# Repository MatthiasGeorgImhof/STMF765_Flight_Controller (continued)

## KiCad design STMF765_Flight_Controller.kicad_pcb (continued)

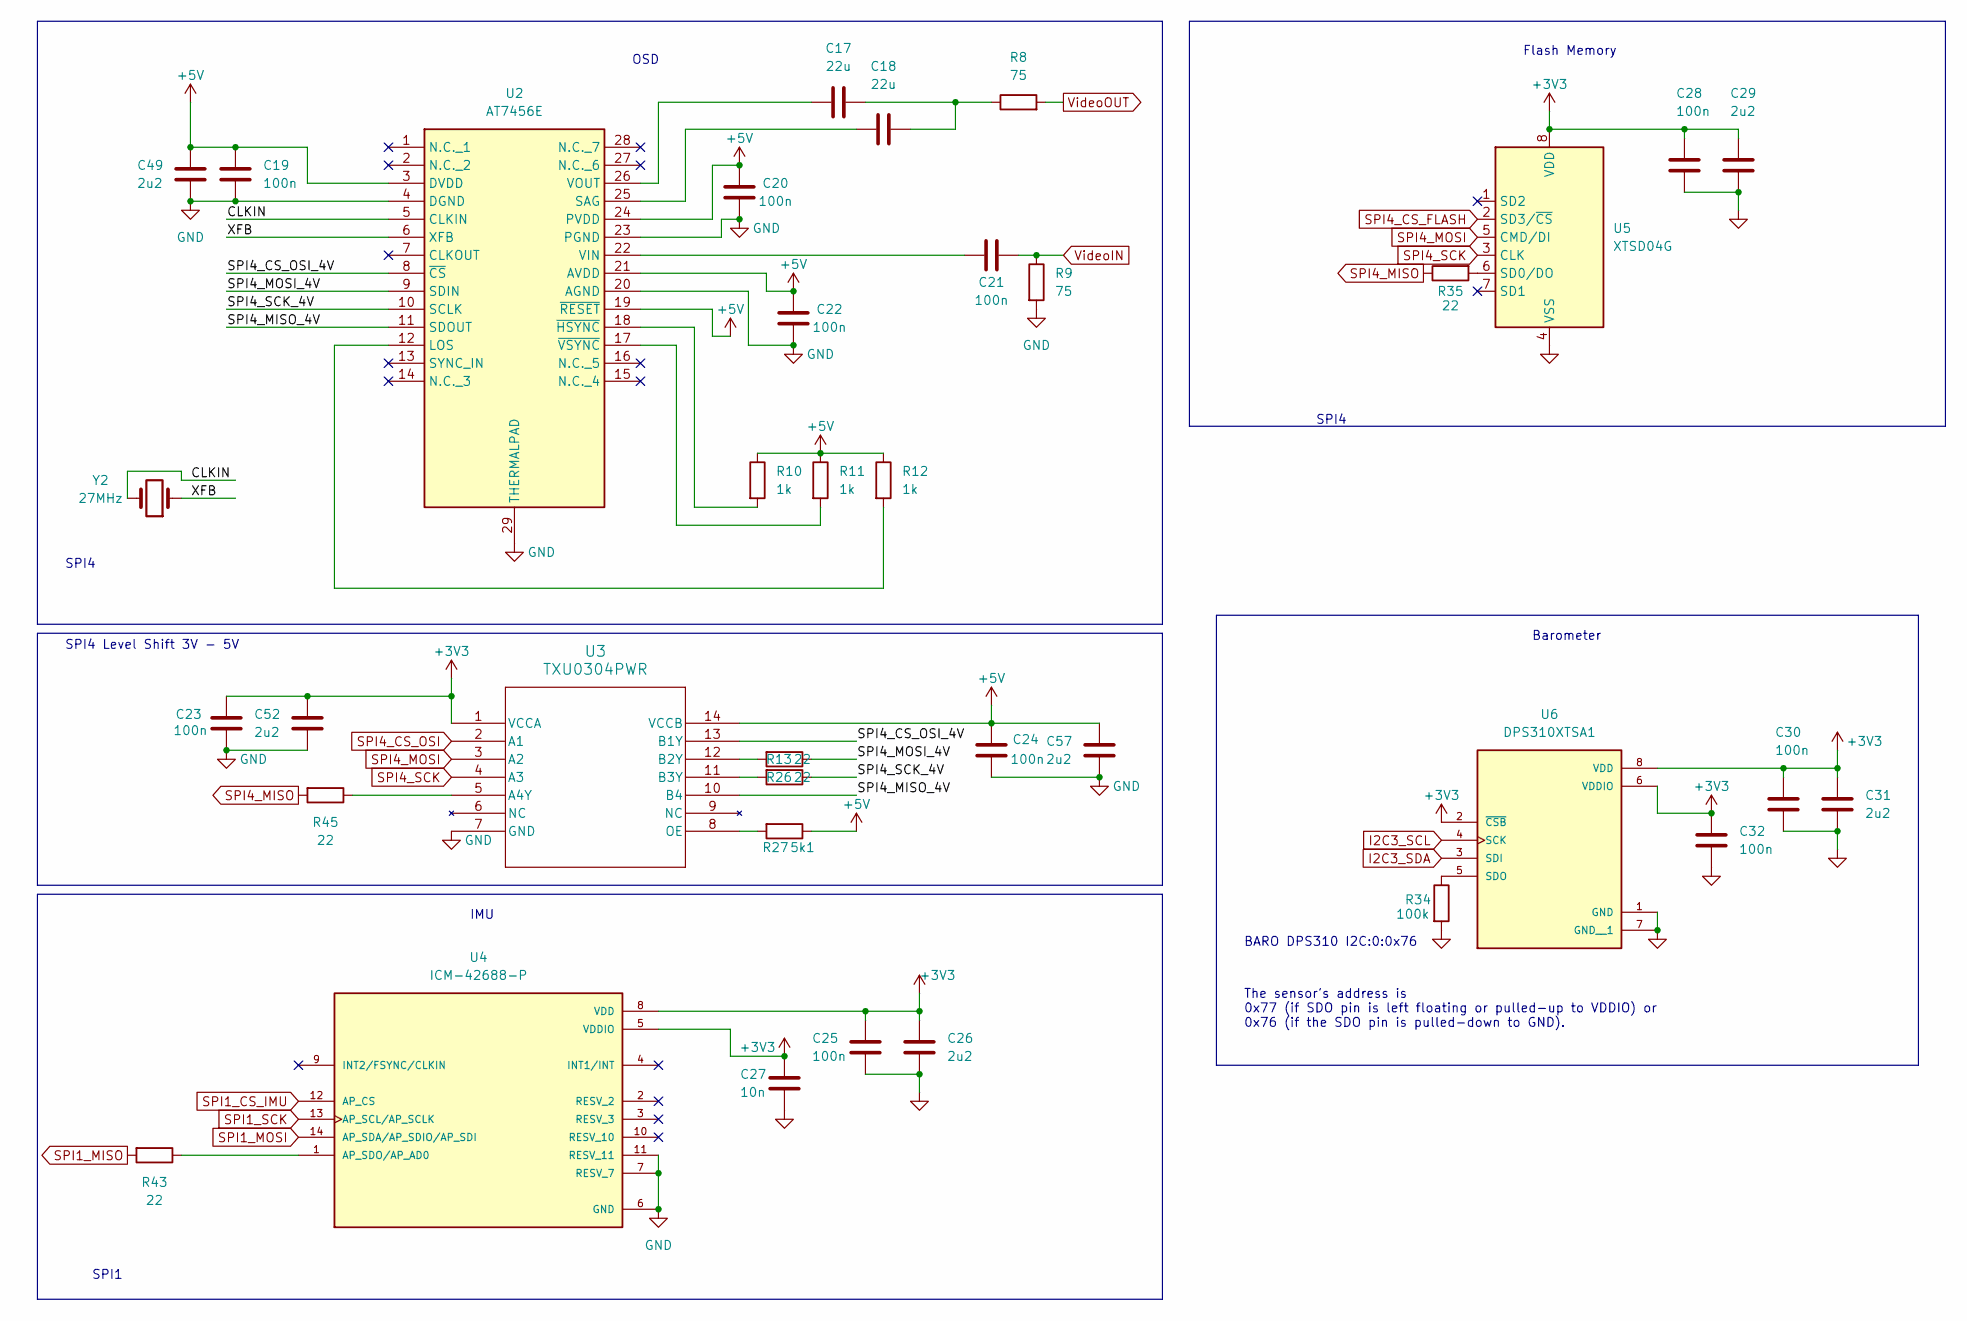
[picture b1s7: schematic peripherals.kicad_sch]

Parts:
C17, C18: 22u; C_1206_3216Metric; Voltage 16; Tolerance 10%; Part Number GRT31CC81C226KE01L
C19, C20, C21, C22, C23, C24, C25, C28, C30, C32: 100n; C_0201_0603Metric; Voltage 16; Tolerance 10%; Part Number GRM033R61C104KE14D
C26, C29, C31, C49, C52, C57: 2u2; C_0402_1005Metric; Voltage 16; Tolerance 10%; Part Number GRM155R61C225KE44D
C27: 10n; C_0201_0603Metric; Voltage 16; Tolerance 10%; Part Number GRM033R61C103KA12D
R8, R9: 75; R_0201_0603Metric; Tolerance 1%; Part Number RC0402FR-0775RP
R10, R11, R12: 1k; R_0201_0603Metric; Tolerance 1%; Part Number RC0402FR-071KL
R13, R26, R35, R43, R45: 22; R_0201_0603Metric; Tolerance 1%; Part Number RC0402FR-0722RP
R27: 5k1; R_0201_0603Metric; Tolerance 1%; Part Number RC0402FR-0722RP
R34: 100k; R_0201_0603Metric; Tolerance 1%; Part Number RC0402FR-0722RP
U2: AT7456E; SOP65P640X120-29N; Part Number AT7456E
U3: TXU0304PWR; TSSOP14_PW_TEX; Part Number TXU0304PWR
U4: ICM-42688-P; PQFN50P300X250X97-14N; Part Number ICM-42688-P
U5: XTSD04G; LGA-8_8x6mm_P1.27mm
U6: DPS310XTSA1; XDCR_DPS310XTSA1; Part Number DPS310XTSA1
Y2: 27MHz; Crystal_SMD_0603-2Pin_6.0x3.5mm; Part Number ECS-270-18-23G-JGN-TR

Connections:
+3V3: C23.2, C25.1, C26.1, C27.1, C28.1, C29.1, C30.1, C31.1, C32.1, C52.1, U3.1 (VCCA), U4.5 (VDDIO), U4.8 (VDD), U5.8 (VDD), U6.2 (~CSB), U6.6 (VDDIO), U6.8 (VDD); also elsewhere on the board
+5V: C19.1, C20.2, C22.2, C24.2, C49.1, C57.1, R10.1, R11.1, R12.1, R27.1, U2.3 (DVDD), U2.19 (~RESET), U2.21 (AVDD), U2.24 (PVDD), U3.14 (VCCB); also elsewhere on the board
/Peripherals/CLKIN: U2.5 (CLKIN), Y2.2
/Peripherals/SPI4_CS_OSI_4V: U2.8 (~CS), U3.13 (B1Y)
/Peripherals/SPI4_MISO_4V: U2.11 (SDOUT), U3.10 (B4)
/Peripherals/SPI4_MOSI_4V: R13.1, U2.9 (SDIN)
/Peripherals/SPI4_SCK_4V: R26.1, U2.10 (SCLK)
/Peripherals/XFB: U2.6 (XFB), Y2.1
GND: C19.2, C20.1, C22.1, C23.1, C24.1, C25.2, C26.2, C27.2, C28.2, C29.2, C30.2, C31.2, C32.2, C49.2, C52.2, C57.2, R9.2, R34.2, U2.4 (DGND), U2.20 (AGND), U2.23 (PGND), U2.29 (THERMALPAD), U3.7 (GND), U4.6 (GND), U4.7 (RESV_7), U4.11 (RESV_11), U5.4 (VSS), U6.1 (GND), U6.7 (GND__1); also elsewhere on the board
I2C3_SCL: U6.4 (SCK); also elsewhere on the board
I2C3_SDA: U6.3 (SDI); also elsewhere on the board
unnamed: C17.2, C18.2, R8.1
unnamed: R12.2, U2.12 (LOS)
unnamed: C18.1, U2.25 (SAG)
unnamed: C21.1, U2.22 (VIN)
unnamed: C17.1, U2.26 (VOUT)
unnamed: R10.2, U2.18 (~HSYNC)
unnamed: R11.2, U2.17 (~VSYNC)
unnamed: R45.1, U3.5 (A4Y)
unnamed: R13.2, U3.12 (B2Y)
unnamed: R26.2, U3.11 (B3Y)
unnamed: R27.2, U3.8 (OE)
unnamed: R43.1, U4.1 (AP_SDO/AP_AD0)
unnamed: R35.2, U5.6 (SD0/DO)
unnamed: R34.1, U6.5 (SDO)
SPI1_CS_IMU: U4.12 (AP_CS); also elsewhere on the board
SPI1_MISO: R43.2; also elsewhere on the board
SPI1_MOSI: U4.14 (AP_SDA/AP_SDIO/AP_SDI); also elsewhere on the board
SPI1_SCK: U4.13 (AP_SCL/AP_SCLK); also elsewhere on the board
SPI4_CS_FLASH: U5.2 (SD3/~CS); also elsewhere on the board
SPI4_CS_OSI: U3.2 (A1); also elsewhere on the board
SPI4_MISO: R35.1, R45.2; also elsewhere on the board
SPI4_MOSI: U3.3 (A2), U5.5 (CMD/DI); also elsewhere on the board
SPI4_SCK: U3.4 (A3), U5.3 (CLK); also elsewhere on the board
VideoIN: C21.2, R9.1; also elsewhere on the board
VideoOUT: R8.2; also elsewhere on the board

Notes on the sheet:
Barometer
OSD
The sensor's address is 0x77 (if SDO pin is left floating or pulled-up to VDDIO) or 0x76 (if the SDO pin is pulled-down to GND).
SPI4
IMU
SPI4 Level Shift 3V - 5V
Flash Memory
SPI1
BARO DPS310 I2C:0:0x76

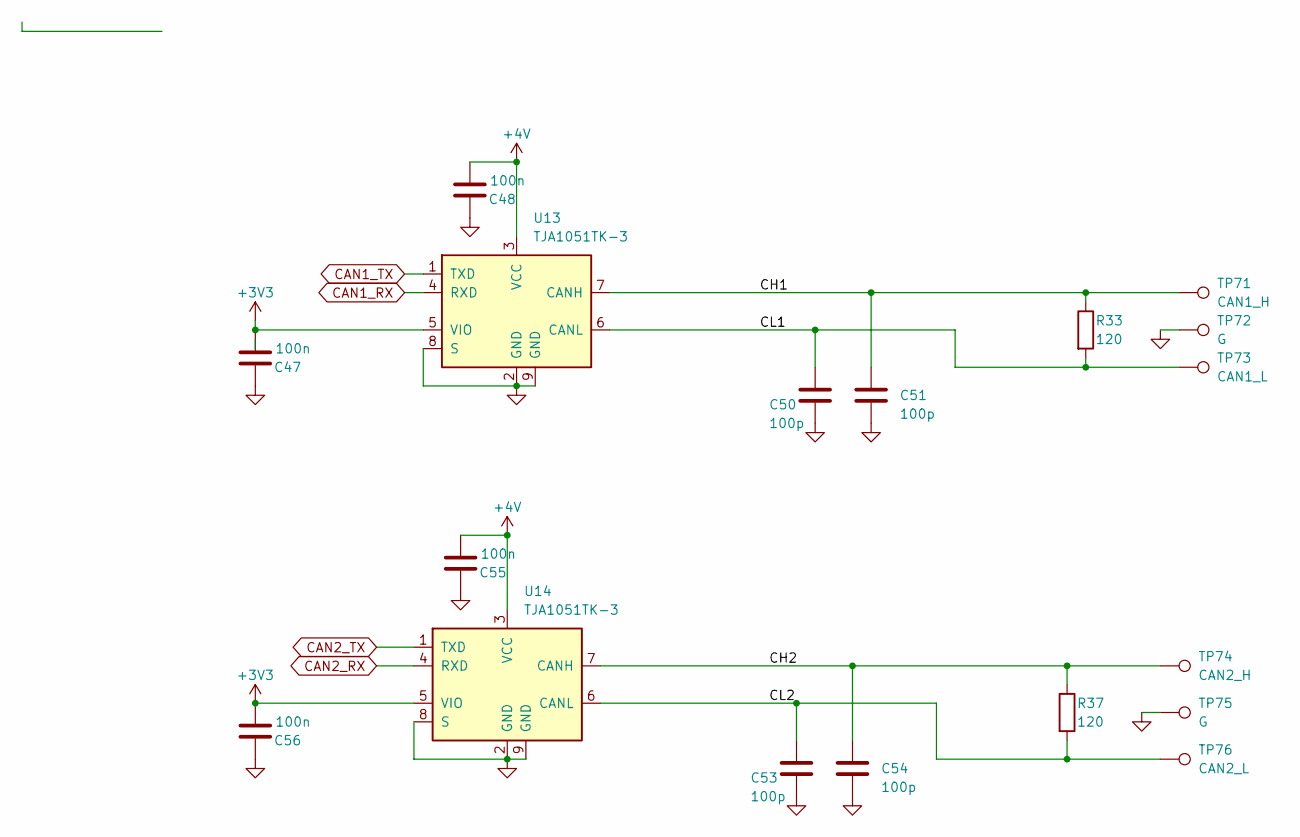
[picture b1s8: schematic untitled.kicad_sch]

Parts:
C47, C48, C55, C56: 100n; C_0201_0603Metric; Voltage 16; Tolerance 10%; Part Number GRM033R61C104KE14D
C50, C51, C53, C54: 100p; C_0201_0603Metric; Voltage 16; Tolerance 10%; Part Number GRM033R71E101KA01D
R33, R37: 120; R_0201_0603Metric; Tolerance 1%; Part Number RC0402FR-0760R4L
TP71: CAN1_H; TestPoint_Pad_1.0x1.5mm
TP72, TP75: G; TestPoint_Pad_1.0x1.5mm
TP73: CAN1_L; TestPoint_Pad_1.0x1.5mm
TP74: CAN2_H; TestPoint_Pad_1.0x1.5mm
TP76: CAN2_L; TestPoint_Pad_1.0x1.5mm
U13, U14: TJA1051TK-3; DFN-8-1EP_3x3mm_P0.65mm_EP1.55x2.4mm; Part Number TJA1051TK-3

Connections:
+3V3: C47.2, C56.2, U13.5 (VIO), U14.5 (VIO); also elsewhere on the board
+4V: C48.2, C55.2, U13.3 (VCC), U14.3 (VCC); also elsewhere on the board
/Pinout for CAN/CH1: C51.1, R33.1, TP71.1, U13.7 (CANH)
/Pinout for CAN/CH2: C54.1, R37.1, TP74.1, U14.7 (CANH)
/Pinout for CAN/CL1: C50.1, R33.2, TP73.1, U13.6 (CANL)
/Pinout for CAN/CL2: C53.1, R37.2, TP76.1, U14.6 (CANL)
CAN1_RX: U13.4 (RXD); also elsewhere on the board
CAN1_TX: U13.1 (TXD); also elsewhere on the board
CAN2_RX: U14.4 (RXD); also elsewhere on the board
CAN2_TX: U14.1 (TXD); also elsewhere on the board
GND: C47.1, C48.1, C50.2, C51.2, C53.2, C54.2, C55.1, C56.1, TP72.1, TP75.1, U13.2 (GND), U13.8 (S), U13.9 (GND), U14.2 (GND), U14.8 (S), U14.9 (GND); also elsewhere on the board

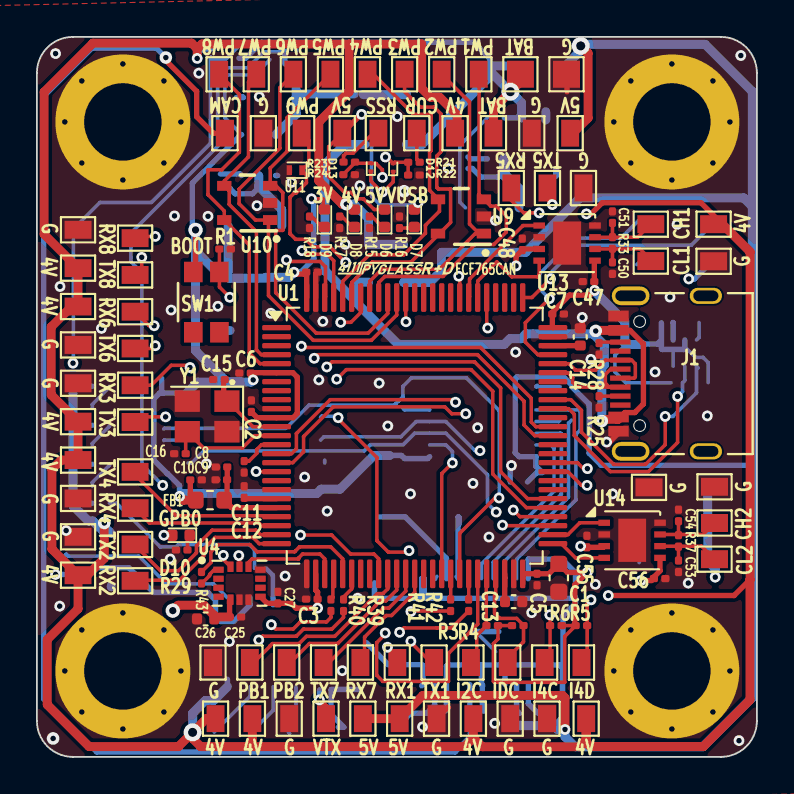
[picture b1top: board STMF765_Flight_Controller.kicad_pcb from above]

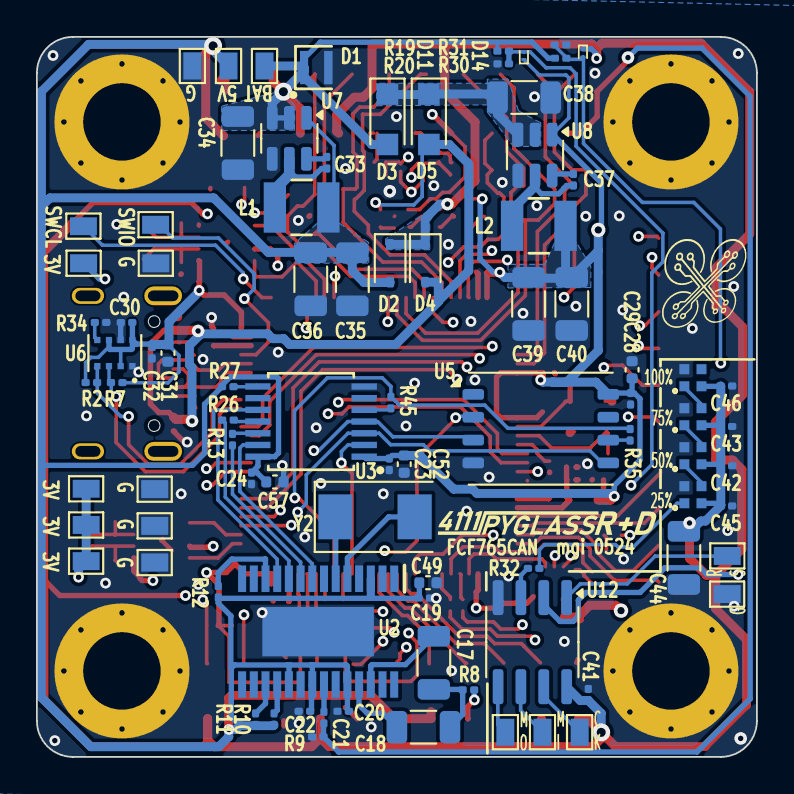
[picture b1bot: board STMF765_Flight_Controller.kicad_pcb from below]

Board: 4 copper layers, 40.0 x 40.0 mm, 232 parts (87 on the bottom side), 122 nets.

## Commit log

2024-07-21 first checkin
2024-07-21 move step files to step folder
2024-07-21 update BOM
2024-07-21 use smaller button
2024-08-01 remove microvias, still need to update silkmasks
2024-08-02 adjust silk screens after microvia replacement
2024-08-07 change flash to sd flash, cleanup, and reconcile with F405FC
